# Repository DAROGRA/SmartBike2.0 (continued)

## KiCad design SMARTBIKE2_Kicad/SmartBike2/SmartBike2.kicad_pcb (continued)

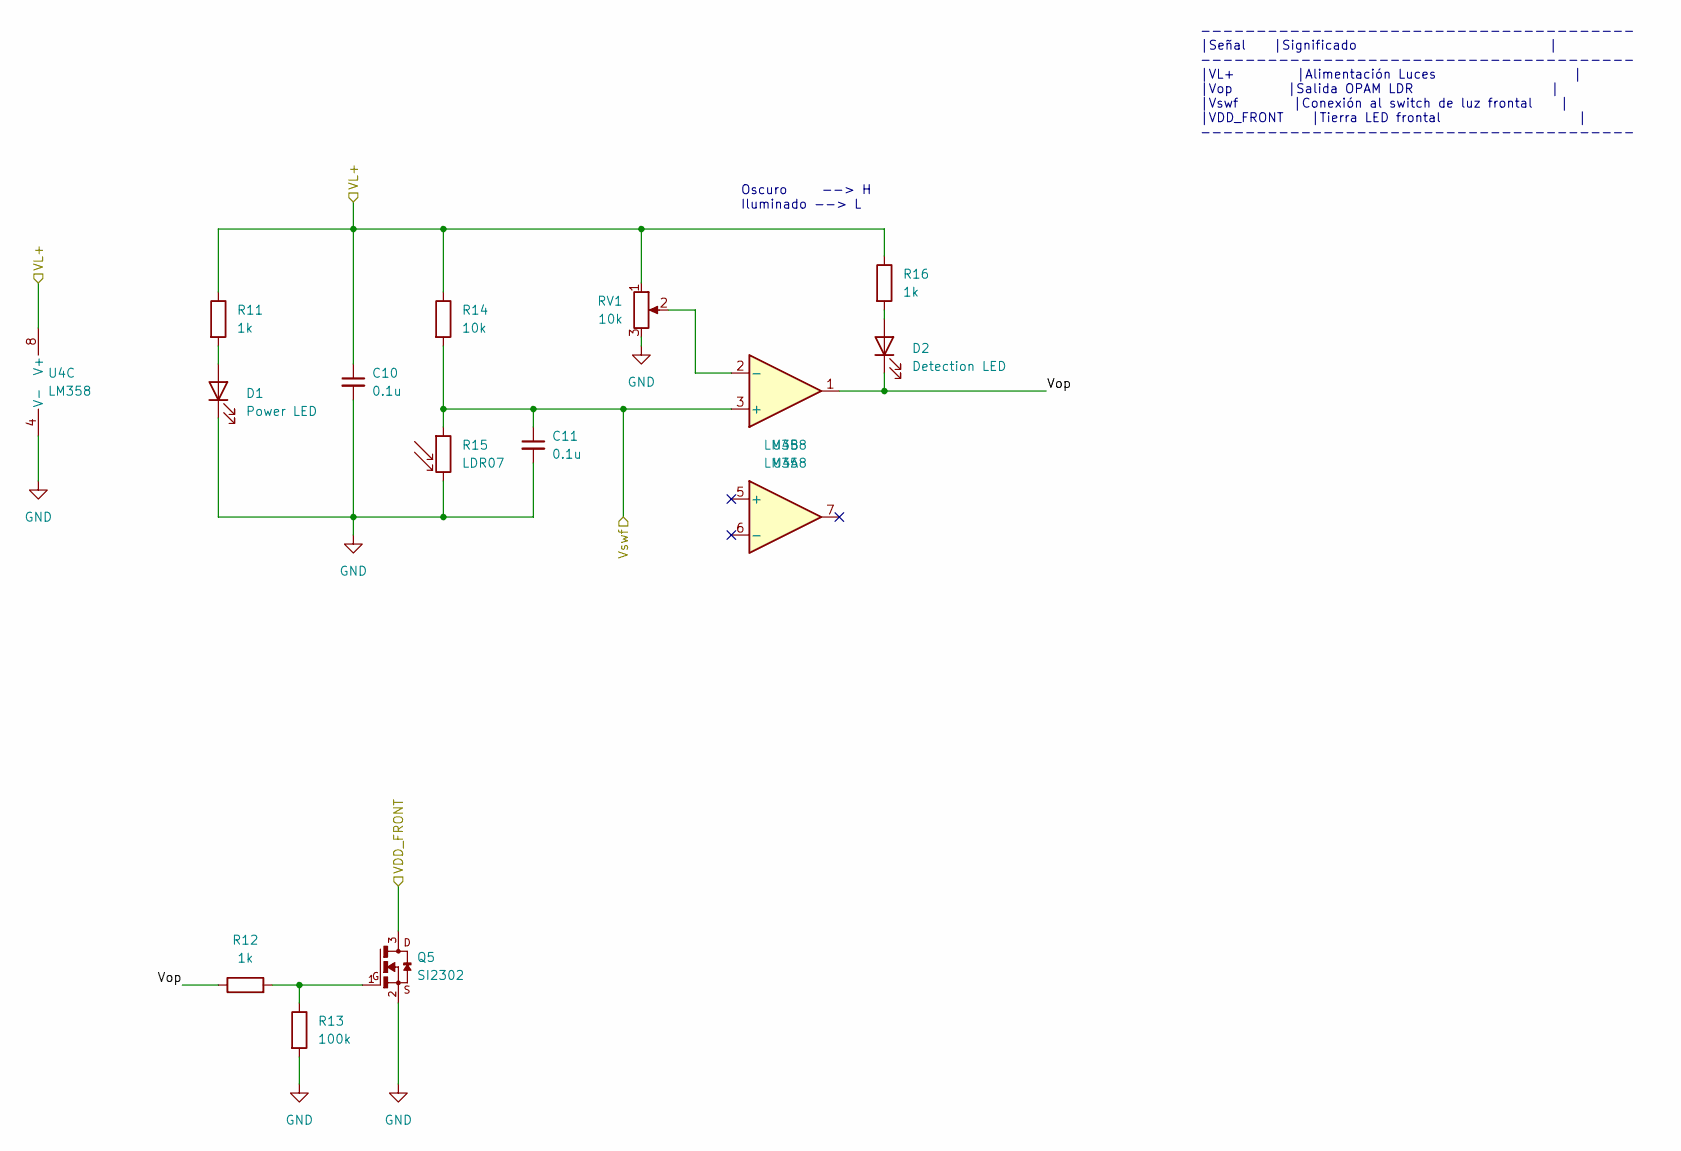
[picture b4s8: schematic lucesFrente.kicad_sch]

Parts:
C10, C11: 0.1u; C_0805_2012Metric_Pad1.18x1.45mm_HandSolder
D1: Power LED; LED_1206_3216Metric_Pad1.42x1.75mm_HandSolder
D2: Detection LED; LED_1206_3216Metric_Pad1.42x1.75mm_HandSolder
Q5: SI2302; SOT-23
R11, R12, R16: 1k; R_0805_2012Metric_Pad1.20x1.40mm_HandSolder
R13: 100k; R_0805_2012Metric_Pad1.20x1.40mm_HandSolder
R14: 10k; R_0805_2012Metric_Pad1.20x1.40mm_HandSolder
R15: LDR07; R_LDR_5.1x4.3mm_P3.4mm_Vertical
RV1: 10k; Potentiometer_Bourns_3386P_Vertical
U4: LM358; SO-8_3.9x4.9mm_P1.27mm

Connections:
/Luces/+VL: C10.1, R11.1, R14.1, R16.1, RV1.1, U4.8 (V+); also elsewhere on the board
/Luces/LucesFrente/VDD_FRONT: Q5.3; also elsewhere on the board
/Luces/LucesFrente/Vop: D2.1 (K), R12.1, U4.1
/Luces/LucesFrente/Vswf: C11.1, R14.2, R15.1, U4.3 (+); also elsewhere on the board
GND: C10.2, C11.2, D1.1 (K), Q5.2, R13.2, R15.2, RV1.3, U4.4 (V-); also elsewhere on the board
unnamed: D1.2 (A), R11.2
unnamed: D2.2 (A), R16.2
unnamed: Q5.1, R12.2, R13.1
unnamed: RV1.2, U4.2 (-)

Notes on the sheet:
Oscuro --> H Iluminado --> L
--------------------------------------- |Señal |Significado | --------------------------------------- |VL+ |Alimentación Luces | |Vop |Salida OPAM LDR | |Vswf |Conexión al switch de luz frontal | |VDD_FRONT |Tierra LED frontal | ---------------------------------------

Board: 2 copper layers, 91 parts (15 on the bottom side), 52 nets, no tracks yet.

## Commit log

2023-10-28 Alimentación 4.1 y Luces
    +) Alimentación SIM800
    + ) Circuitos control Luces
    P) Circuito Parlante
    P) Alimentación 3.3V
2023-10-30 Revisión conjunta 29/10/23
    Llamen a Dios
2023-10-30 Siempre cierren kicad :(
2023-11-05 Alimentación ESP32
2023-11-06 Alarma, luces frontales y modulos
    + Circuito luces frontales
    + Conector Luces
    + Conector GPS
    + Conector SIM
    + Conector acelerómetro
    ~ Acondicionamiento ESP32
2023-11-07 Simbolo ESP32
2023-11-07 Beta 100% esquemáticos
    + Acondicionamiento ESP32
    ~ Huellas
    ~ PCB
2023-11-07 Backup Kicad automático
2023-11-08 autosave
2023-11-09 cambio alimentacion GPS
2023-11-10 Huellas
2023-11-10 cache
2023-11-10 empiece el caos y el descontrol
2023-11-10 Revert "Huellas"
    This reverts commit aca3b90f662b4b3f1bd5f85dc2a5dccaf30f2ab1.
2023-11-10 Mas huellas
2023-11-10 Final Huellas
2023-11-10 diseño PCB1.0
2023-11-10 cache inservible
2023-11-10 Arreglo
2023-11-12 Fase 1 panel
2023-11-12 Fase 2 de 3 panel
    + Esquemático Alimentación y Alarma
    + PCB 1 de 3, Alimentación y Alarma
    + Esquemático Acondicionamiento y Conexión módulos
    ~ PCB 2 de 3 Acondicionamiento y Conexión módulos
    ~ Esquemático Luces
    ~ PCB 3 de 3, Luces
2023-11-13 Fase 2 de 3 panel full
    + PCB Acondicionamiento y Módulos
    ~ Esquemático Luces
    ~ PCB 3 de 3, Luces
    ~ Panelización
2023-11-13 Esquemático Luces
2023-11-13 PCB 3 de 3
    +PCB 3 de 3, Luces
    ~Panelización
2023-11-14 Gerbers PCB
    Se combinaron todas las PCB en una sola placa para ser cortada manualmente con un espacio entre placas de 1cm.
    Estos archivos se encuentran en la carpeta de "GerbersSB2"
2023-11-14 PDF F.CU y B.CU
2023-11-15 Backup
2023-11-16 Impresión vías sin metalización
2023-12-05 Cambios Finales
